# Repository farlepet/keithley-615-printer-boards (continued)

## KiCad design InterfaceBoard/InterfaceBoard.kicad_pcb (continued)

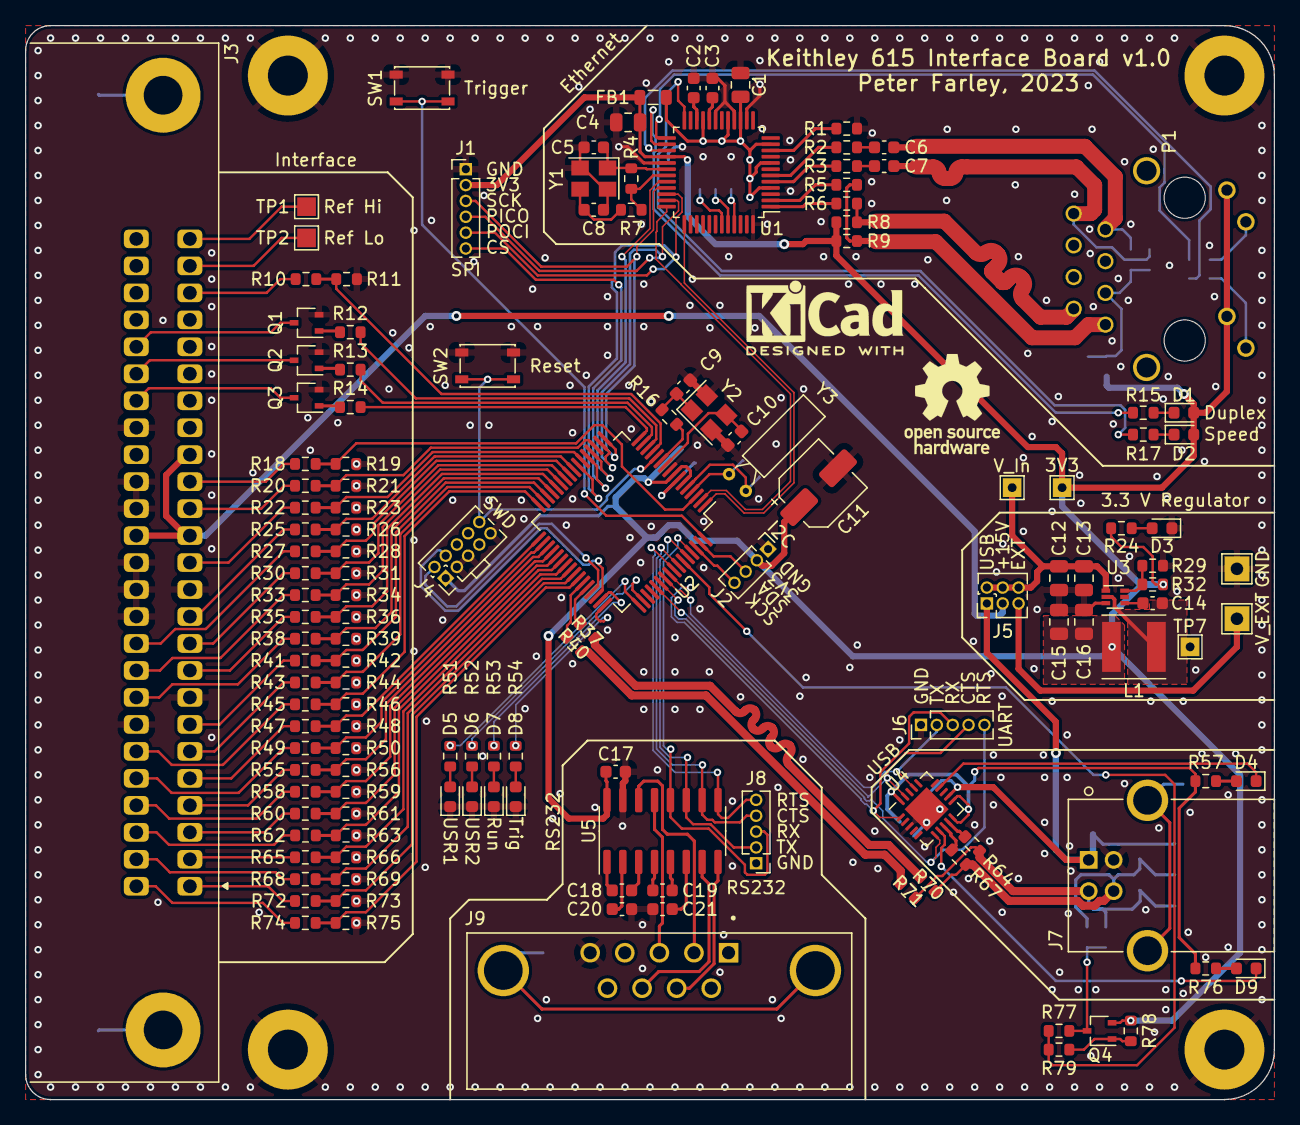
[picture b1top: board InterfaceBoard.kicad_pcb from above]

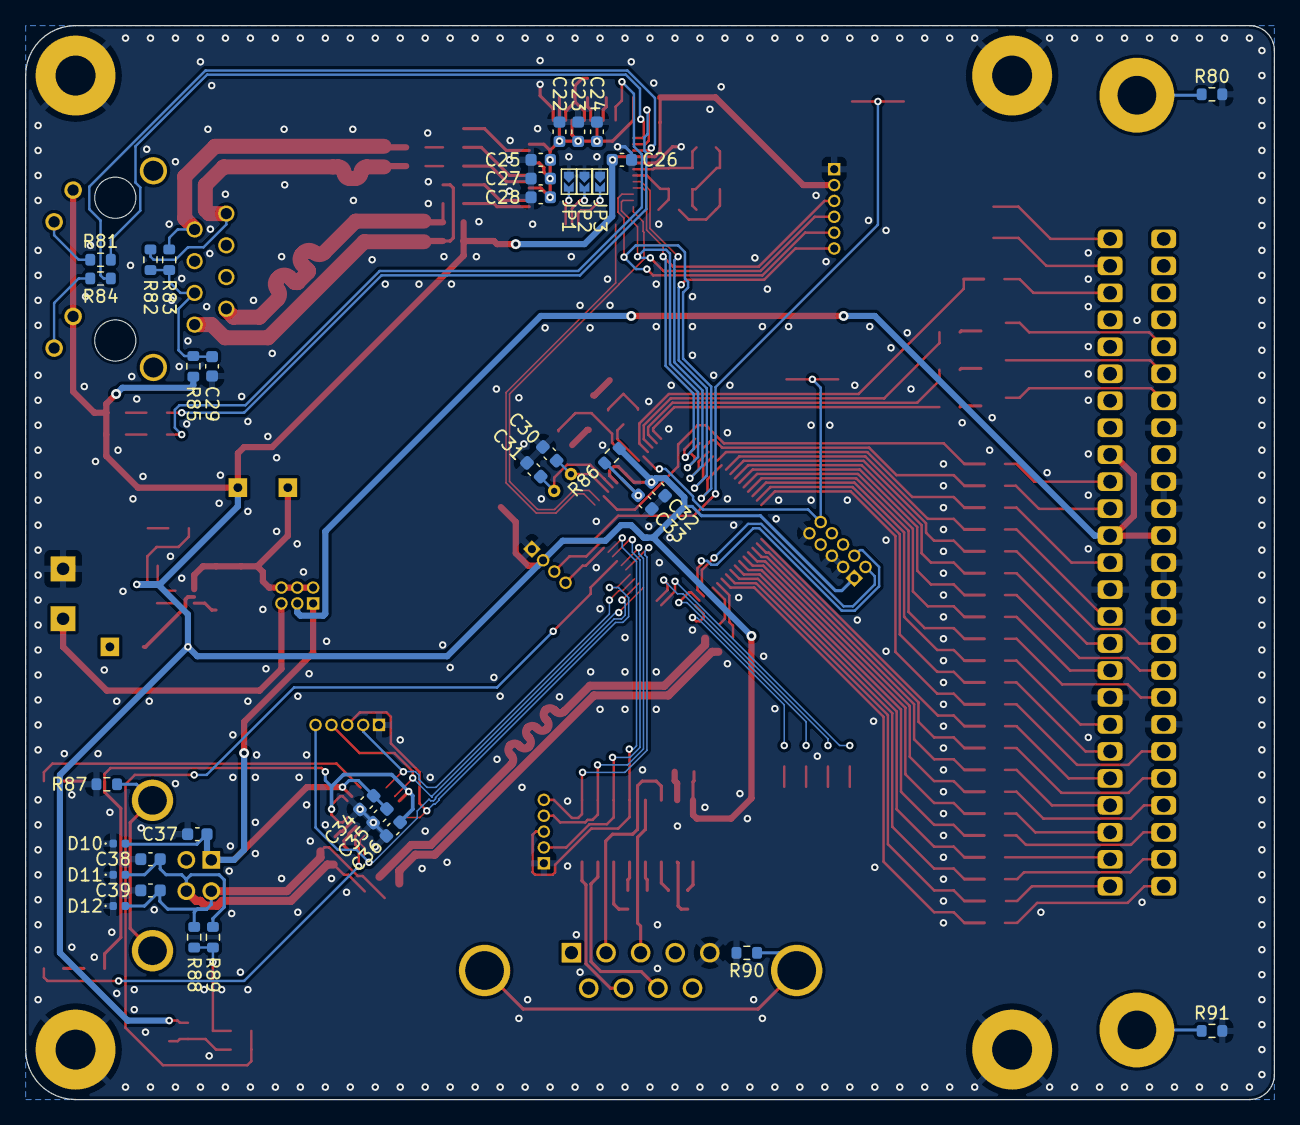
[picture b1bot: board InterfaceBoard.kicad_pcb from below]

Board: 2 copper layers, 100.0 x 86.0 mm, 182 parts (36 on the bottom side), 161 nets.

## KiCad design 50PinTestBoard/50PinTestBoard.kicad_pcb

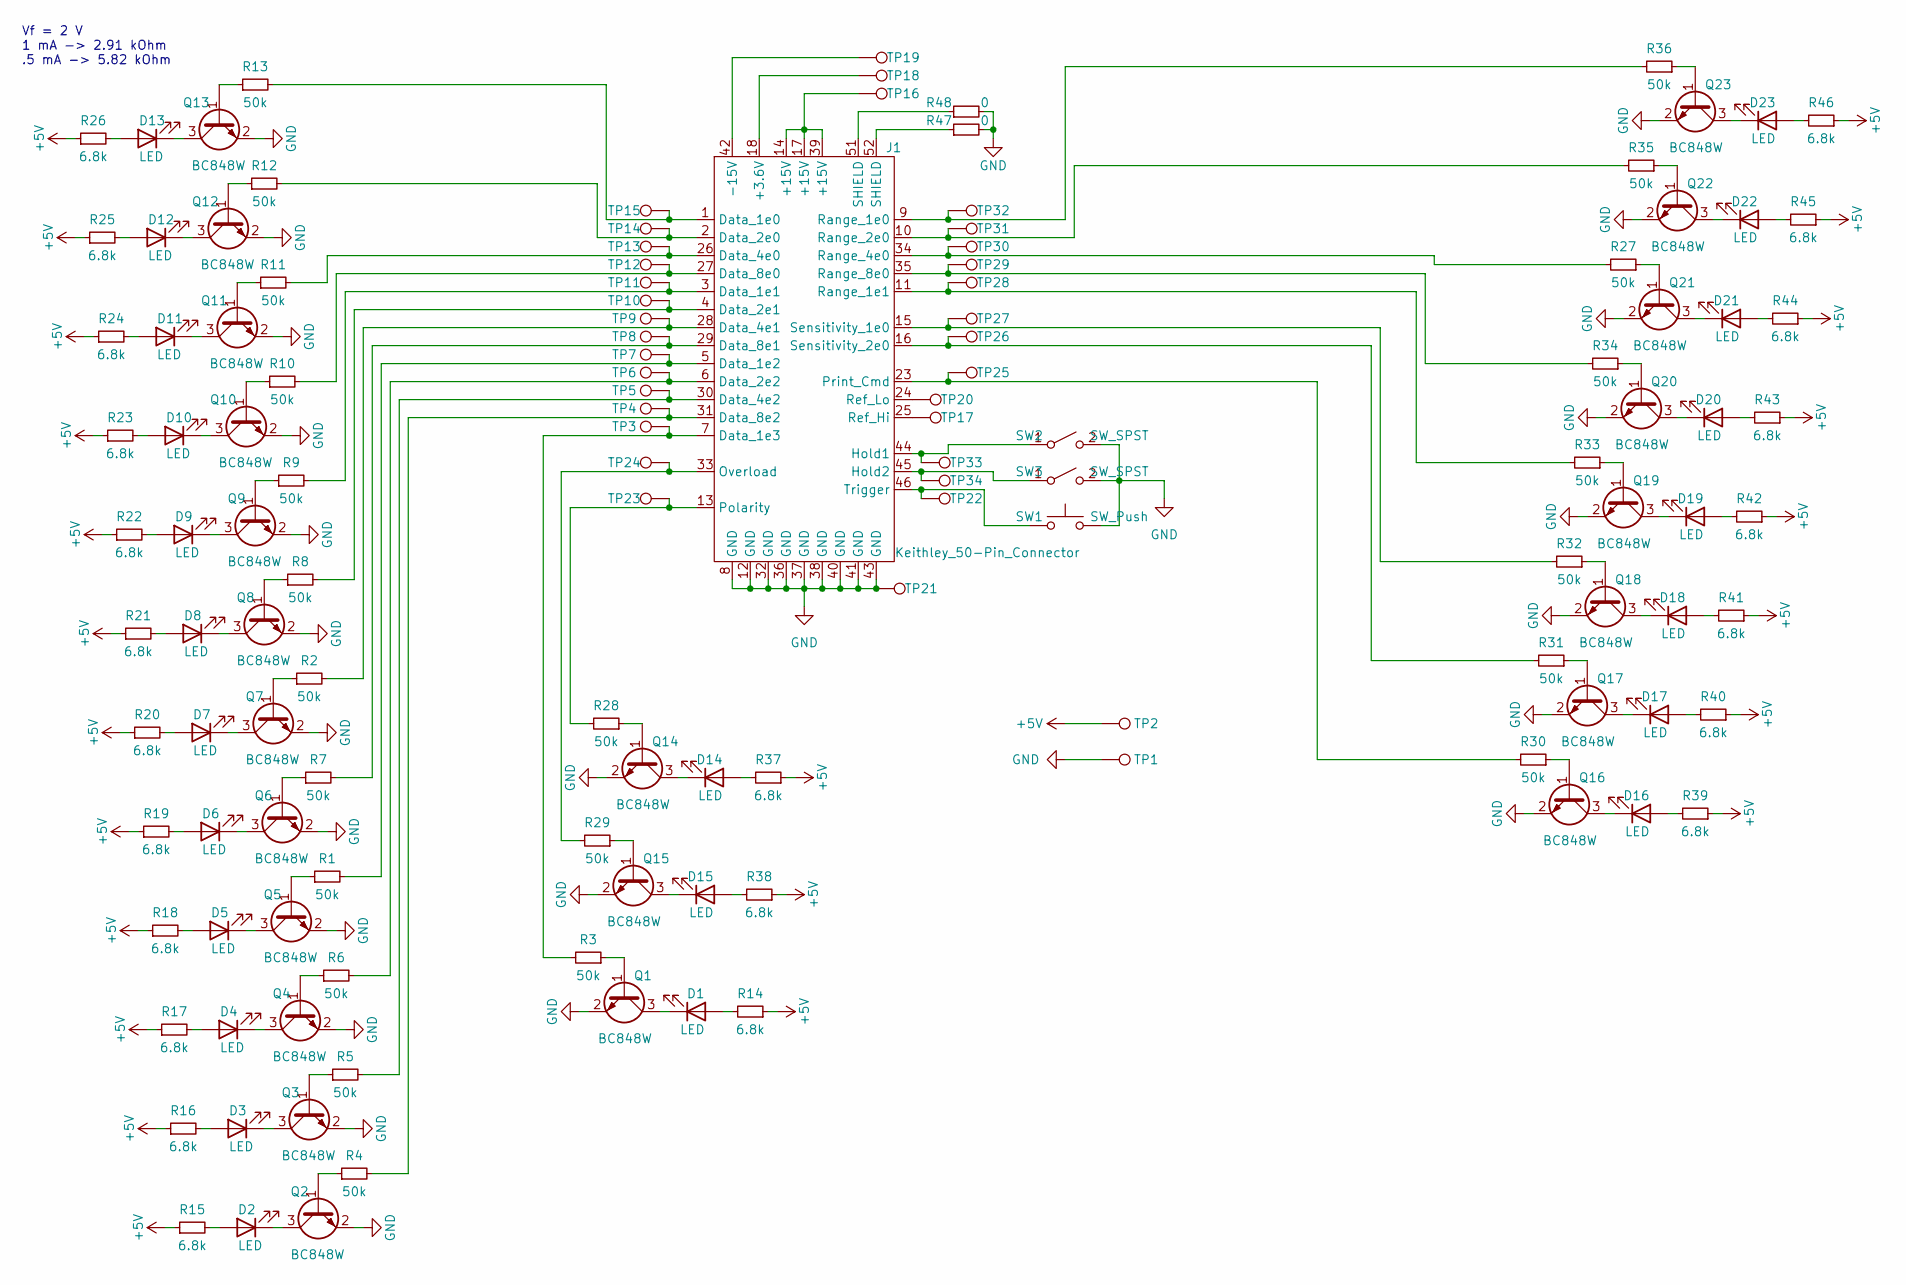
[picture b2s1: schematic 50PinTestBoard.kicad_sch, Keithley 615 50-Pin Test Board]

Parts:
D1, D2, D3, D4, D5, D6, D7, D8, D9, D10, D11, D12, D13, D14, D15, D16, D17, D18, D19, D20, D21, D22, D23: LED; LED_0603_1608Metric
J1: Keithley_50-Pin_Connector; NorComp_112-050-213R001
Q1, Q2, Q3, Q4, Q5, Q6, Q7, Q8, Q9, Q10, Q11, Q12, Q13, Q14, Q15, Q16, Q17, Q18, Q19, Q20, Q21, Q22, Q23: BC848W; SOT-323_SC-70
R1, R2, R3, R4, R5, R6, R7, R8, R9, R10, R11, R12, R13, R27, R28, R29, R30, R31, R32, R33, R34, R35, R36: 50k; R_0603_1608Metric
R14, R15, R16, R17, R18, R19, R20, R21, R22, R23, R24, R25, R26, R37, R38, R39, R40, R41, R42, R43, R44, R45, R46: 6.8k; R_0603_1608Metric
R47, R48: 0; R_0603_1608Metric
SW1: SW_Push; SW_SPST_PTS810
SW2, SW3: SW_SPST; SW_SPDT_CK-JS102011SAQN
TP1, TP2, TP3, TP4, TP5, TP6, TP7, TP8, TP9, TP10, TP11, TP12, TP13, TP14, TP15, TP16, TP17, TP18, TP19, TP20, TP21, TP22, TP23, TP24, TP25, TP26, TP27, TP28, TP29, TP30, TP31, TP32, TP33, TP34: TestPoint; TestPoint_THTPad_2.0x2.0mm_Drill1.0mm

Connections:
+5V: R14.1, R15.1, R16.1, R17.1, R18.1, R19.1, R20.1, R21.1, R22.1, R23.1, R24.1, R25.1, R26.1, R37.1, R38.1, R39.1, R40.1, R41.1, R42.1, R43.1, R44.1, R45.1, R46.1, TP2.1
GND: J1.8 (GND), J1.12 (GND), J1.32 (GND), J1.36 (GND), J1.37 (GND), J1.38 (GND), J1.40 (GND), J1.41 (GND), J1.43 (GND), Q1.2 (E), Q2.2 (E), Q3.2 (E), Q4.2 (E), Q5.2 (E), Q6.2 (E), Q7.2 (E), Q8.2 (E), Q9.2 (E), Q10.2 (E), Q11.2 (E), Q12.2 (E), Q13.2 (E), Q14.2 (E), Q15.2 (E), Q16.2 (E), Q17.2 (E), Q18.2 (E), Q19.2 (E), Q20.2 (E), Q21.2 (E), Q22.2 (E), Q23.2 (E), R47.2, R48.2, SW1.2, SW2.2 (B), SW3.2 (B), TP1.1, TP21.1
unnamed: D1.1 (K), Q1.3 (C)
unnamed: D1.2 (A), R14.2
unnamed: D2.1 (K), Q2.3 (C)
unnamed: D2.2 (A), R15.2
unnamed: D3.1 (K), Q3.3 (C)
unnamed: D3.2 (A), R16.2
unnamed: D4.1 (K), Q4.3 (C)
unnamed: D4.2 (A), R17.2
unnamed: D5.1 (K), Q5.3 (C)
unnamed: D5.2 (A), R18.2
unnamed: D6.1 (K), Q6.3 (C)
unnamed: D6.2 (A), R19.2
unnamed: D7.1 (K), Q7.3 (C)
unnamed: D7.2 (A), R20.2
unnamed: D8.1 (K), Q8.3 (C)
unnamed: D8.2 (A), R21.2
unnamed: D9.1 (K), Q9.3 (C)
unnamed: D9.2 (A), R22.2
unnamed: D10.1 (K), Q10.3 (C)
unnamed: D10.2 (A), R23.2
unnamed: D11.1 (K), Q11.3 (C)
unnamed: D11.2 (A), R24.2
unnamed: D12.1 (K), Q12.3 (C)
unnamed: D12.2 (A), R25.2
unnamed: D13.1 (K), Q13.3 (C)
unnamed: D13.2 (A), R26.2
unnamed: D14.1 (K), Q14.3 (C)
unnamed: D14.2 (A), R37.2
unnamed: D15.1 (K), Q15.3 (C)
unnamed: D15.2 (A), R38.2
unnamed: D16.1 (K), Q16.3 (C)
unnamed: D16.2 (A), R39.2
unnamed: D17.1 (K), Q17.3 (C)
unnamed: D17.2 (A), R40.2
unnamed: D18.1 (K), Q18.3 (C)
unnamed: D18.2 (A), R41.2
unnamed: D19.1 (K), Q19.3 (C)
unnamed: D19.2 (A), R42.2
unnamed: D20.1 (K), Q20.3 (C)
unnamed: D20.2 (A), R43.2
unnamed: D21.1 (K), Q21.3 (C)
unnamed: D21.2 (A), R44.2
unnamed: D22.1 (K), Q22.3 (C)
unnamed: D22.2 (A), R45.2
unnamed: D23.1 (K), Q23.3 (C)
unnamed: D23.2 (A), R46.2
unnamed: J1.1 (Data_1e0), R13.2, TP15.1
unnamed: J1.2 (Data_2e0), R12.2, TP14.1
unnamed: J1.3 (Data_1e1), R9.2, TP11.1
unnamed: J1.4 (Data_2e1), R8.2, TP10.1
unnamed: J1.5 (Data_1e2), R1.2, TP7.1
unnamed: J1.6 (Data_2e2), R6.2, TP6.1
unnamed: J1.7 (Data_1e3), R3.2, TP3.1
unnamed: J1.9 (Range_1e0), R36.2, TP32.1
unnamed: J1.10 (Range_2e0), R35.2, TP31.1
unnamed: J1.11 (Range_1e1), R33.2, TP28.1
unnamed: J1.13 (Polarity), R28.2, TP23.1
unnamed: J1.14 (+15V), J1.17 (+15V), J1.39 (+15V), TP16.1
unnamed: J1.15 (Sensitivity_1e0), R32.2, TP27.1
unnamed: J1.16 (Sensitivity_2e0), R31.2, TP26.1
unnamed: J1.18 (+3.6V), TP18.1
unnamed: J1.23 (Print_Cmd), R30.2, TP25.1
unnamed: J1.24 (Ref_Lo), TP20.1
unnamed: J1.25 (Ref_Hi), TP17.1
unnamed: J1.26 (Data_4e0), R11.2, TP13.1
unnamed: J1.27 (Data_8e0), R10.2, TP12.1
unnamed: J1.28 (Data_4e1), R2.2, TP9.1
unnamed: J1.29 (Data_8e1), R7.2, TP8.1
unnamed: J1.30 (Data_4e2), R5.2, TP5.1
unnamed: J1.31 (Data_8e2), R4.2, TP4.1
unnamed: J1.33 (Overload), R29.2, TP24.1
unnamed: J1.34 (Range_4e0), R27.2, TP30.1
unnamed: J1.35 (Range_8e0), R34.2, TP29.1
unnamed: J1.42 (-15V), TP19.1
unnamed: J1.44 (Hold1), SW2.1 (A), TP33.1
unnamed: J1.45 (Hold2), SW3.1 (A), TP34.1
unnamed: J1.46 (Trigger), SW1.1, TP22.1
unnamed: J1.51 (SHIELD), R48.1
unnamed: J1.52 (SHIELD), R47.1
unnamed: Q1.1 (B), R3.1
unnamed: Q2.1 (B), R4.1
unnamed: Q3.1 (B), R5.1
unnamed: Q4.1 (B), R6.1
unnamed: Q5.1 (B), R1.1
unnamed: Q6.1 (B), R7.1
unnamed: Q7.1 (B), R2.1
unnamed: Q8.1 (B), R8.1
unnamed: Q9.1 (B), R9.1
unnamed: Q10.1 (B), R10.1
unnamed: Q11.1 (B), R11.1
unnamed: Q12.1 (B), R12.1
unnamed: Q13.1 (B), R13.1
unnamed: Q14.1 (B), R28.1
unnamed: Q15.1 (B), R29.1
unnamed: Q16.1 (B), R30.1
unnamed: Q17.1 (B), R31.1
unnamed: Q18.1 (B), R32.1
unnamed: Q19.1 (B), R33.1
unnamed: Q20.1 (B), R34.1
unnamed: Q21.1 (B), R27.1
unnamed: Q22.1 (B), R35.1
unnamed: Q23.1 (B), R36.1

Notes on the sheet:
Vf = 2 V 1 mA -> 2.91 kOhm .5 mA -> 5.82 kOhm

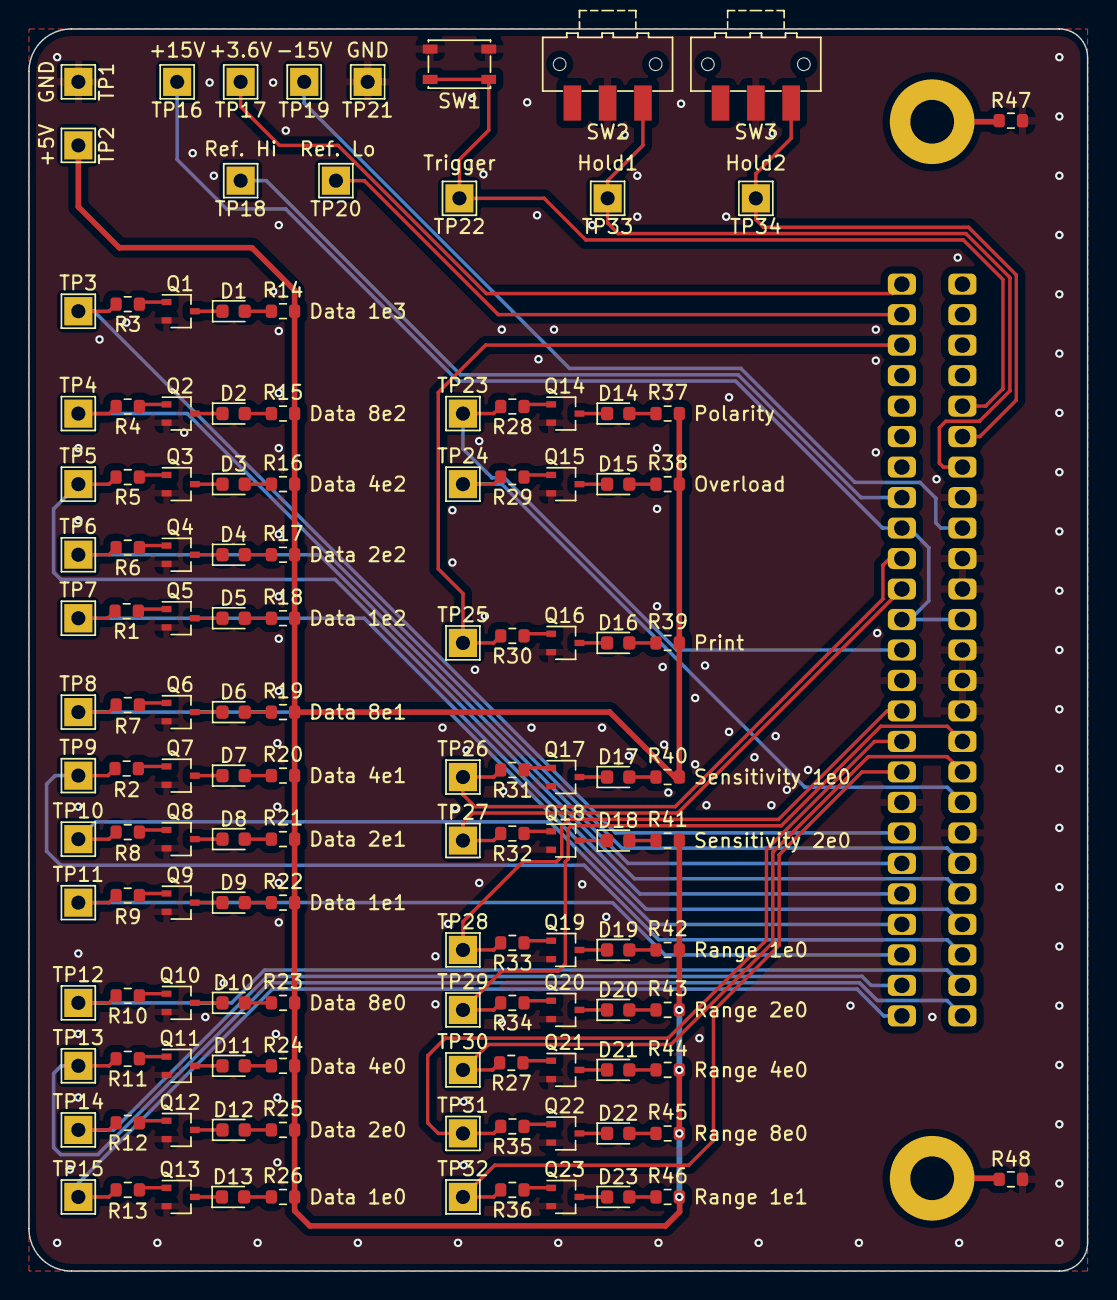
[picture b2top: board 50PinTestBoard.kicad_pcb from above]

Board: 2 copper layers, 75.0 x 88.0 mm, 132 parts (1 on the bottom side), 104 nets.

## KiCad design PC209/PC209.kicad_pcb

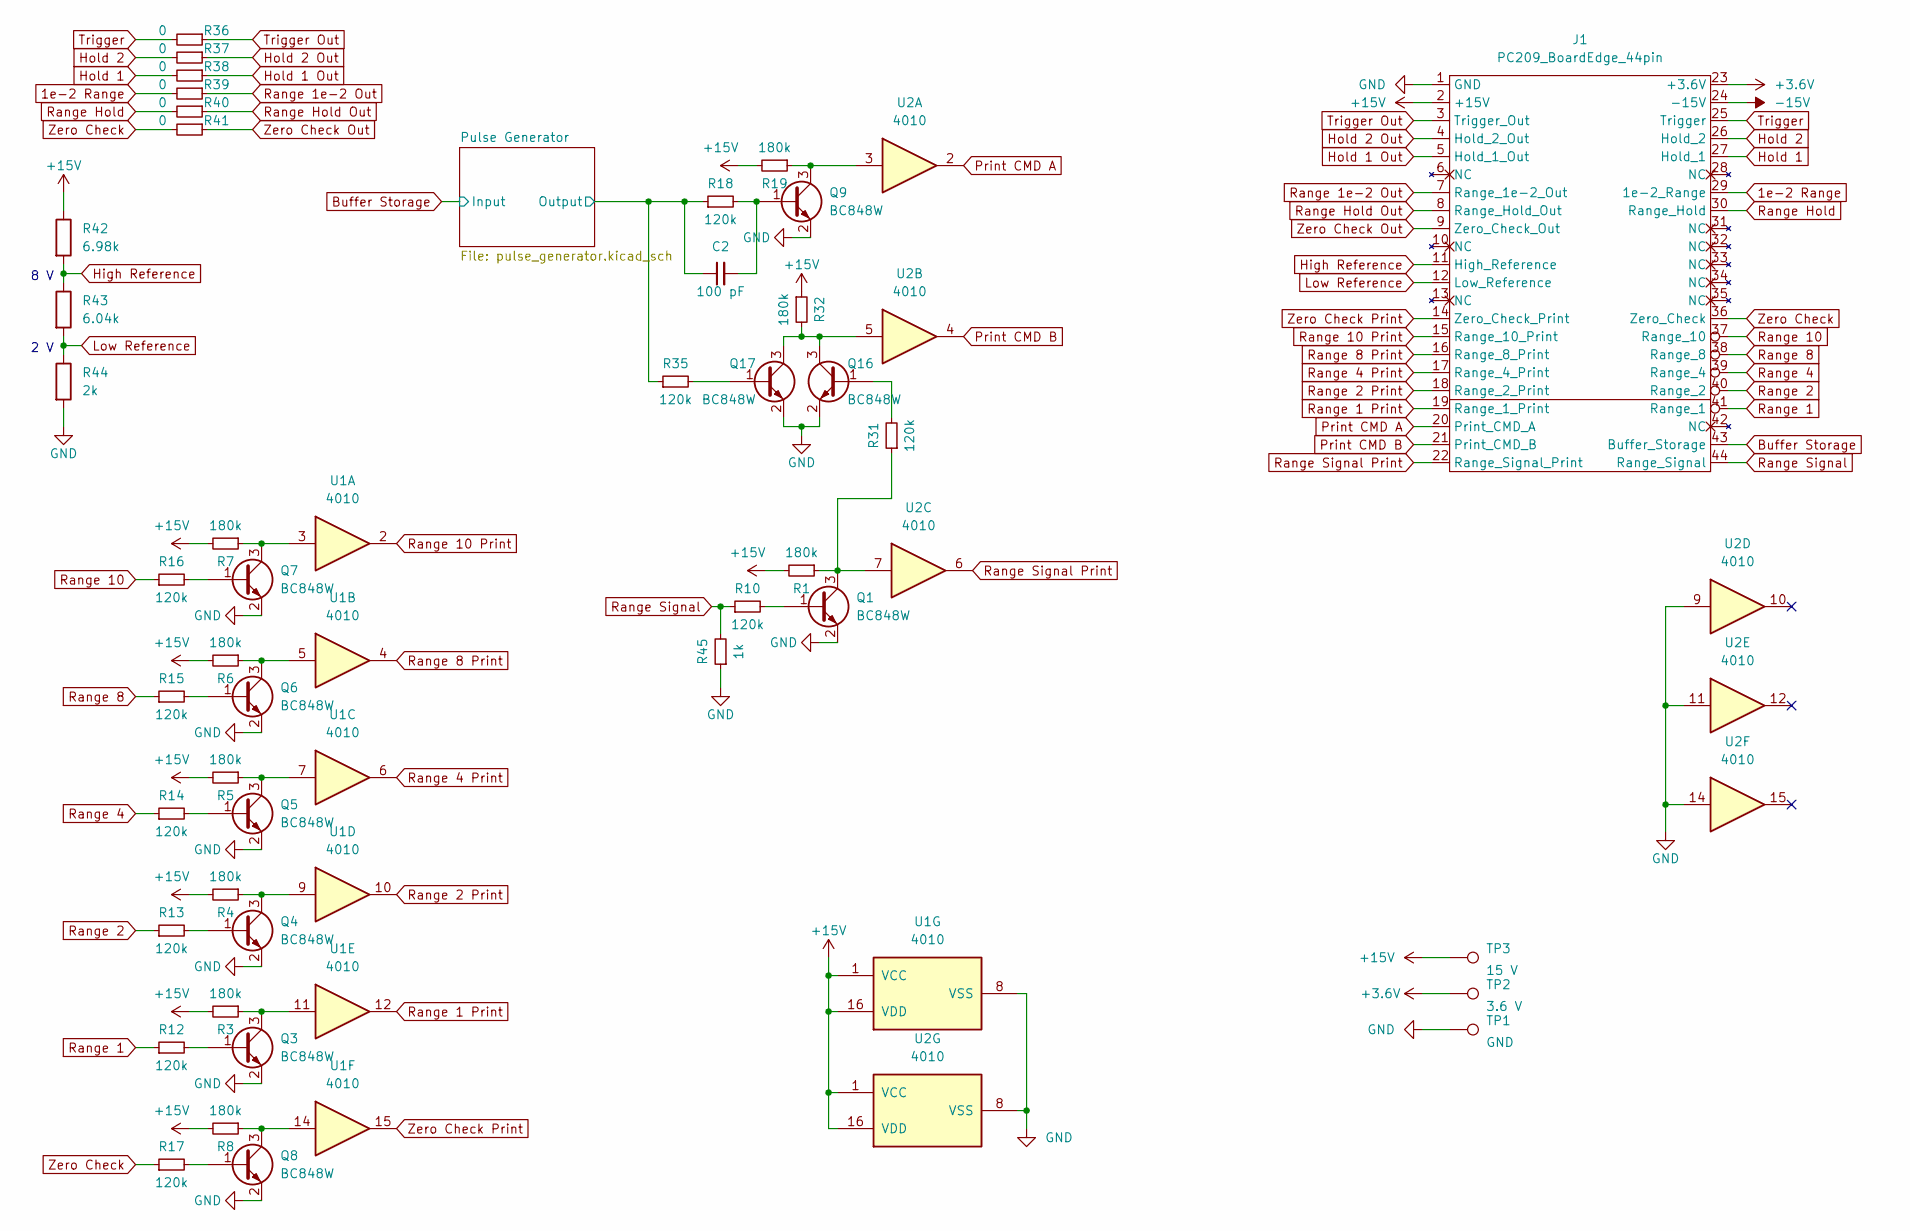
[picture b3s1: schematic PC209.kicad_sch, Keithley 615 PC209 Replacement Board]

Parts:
C2: 100 pF; C_0603_1608Metric
J1: PC209_BoardEdge_44pin; PC209_Edge_Connector
Q1, Q3, Q4, Q5, Q6, Q7, Q8, Q9, Q16, Q17: BC848W; SOT-323_SC-70
R1, R3, R4, R5, R6, R7, R8, R19, R32: 180k; R_0603_1608Metric
R10, R12, R13, R14, R15, R16, R17, R18, R31, R35: 120k; R_0603_1608Metric
R36, R37, R38, R39, R40, R41: 0; R_0603_1608Metric
R42: 6.98k; R_0603_1608Metric
R43: 6.04k; R_0603_1608Metric
R44: 2k; R_0603_1608Metric
R45: 1k; R_0603_1608Metric
TP1: GND; TestPoint_THTPad_2.0x2.0mm_Drill1.0mm
TP2: 3.6 V; TestPoint_THTPad_2.0x2.0mm_Drill1.0mm
TP3: 15 V; TestPoint_THTPad_2.0x2.0mm_Drill1.0mm
U1, U2: 4010; SOIC-16_3.9x9.9mm_P1.27mm

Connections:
1e-2 Range: J1.29 (1e-2_Range), R39.2
+3.6V: J1.23 (+3.6V), TP2.1; also elsewhere on the board
+15V: J1.2 (+15V), R1.2, R3.2, R4.2, R5.2, R6.2, R7.2, R8.2, R19.2, R32.1, R42.1, TP3.1, U1.1 (VCC), U1.16 (VDD), U2.1 (VCC), U2.16 (VDD)
-15V: J1.24 (-15V)
/Pulse Generator/Output: C2.1, R18.1, R35.1; also elsewhere on the board
Buffer Storage: J1.43 (Buffer_Storage); also elsewhere on the board
GND: J1.1 (GND), Q1.2 (E), Q3.2 (E), Q4.2 (E), Q5.2 (E), Q6.2 (E), Q7.2 (E), Q8.2 (E), Q9.2 (E), Q16.2 (E), Q17.2 (E), R44.2, R45.1, TP1.1, U1.8 (VSS), U2.8 (VSS), U2.9, U2.11, U2.14; also elsewhere on the board
High Reference: J1.11 (High_Reference), R42.2, R43.1
Hold 1: J1.27 (Hold_1), R38.2
Hold 1 Out: J1.5 (Hold_1_Out), R38.1
Hold 2: J1.26 (Hold_2), R37.2
Hold 2 Out: J1.4 (Hold_2_Out), R37.1
Low Reference: J1.12 (Low_Reference), R43.2, R44.1
unnamed: C2.2, Q9.1 (B), R18.2
unnamed: Q1.1 (B), R10.2
unnamed: Q1.3 (C), R1.1, R31.1, U2.7
unnamed: Q3.1 (B), R12.2
unnamed: Q3.3 (C), R3.1, U1.11
unnamed: Q4.1 (B), R13.2
unnamed: Q4.3 (C), R4.1, U1.9
unnamed: Q5.1 (B), R14.2
unnamed: Q5.3 (C), R5.1, U1.7
unnamed: Q6.1 (B), R15.2
unnamed: Q6.3 (C), R6.1, U1.5
unnamed: Q7.1 (B), R16.2
unnamed: Q7.3 (C), R7.1, U1.3
unnamed: Q8.1 (B), R17.2
unnamed: Q8.3 (C), R8.1, U1.14
unnamed: Q9.3 (C), R19.1, U2.3
unnamed: Q16.1 (B), R31.2
unnamed: Q16.3 (C), Q17.3 (C), R32.2, U2.5
unnamed: Q17.1 (B), R35.2
Print CMD A: J1.20 (Print_CMD_A), U2.2
Print CMD B: J1.21 (Print_CMD_B), U2.4
Range 1: J1.41 (Range_1), R12.1
Range 1 Print: J1.19 (Range_1_Print), U1.12
Range 1e-2 Out: J1.7 (Range_1e-2_Out), R39.1
Range 2: J1.40 (Range_2), R13.1
Range 2 Print: J1.18 (Range_2_Print), U1.10
Range 4: J1.39 (Range_4), R14.1
Range 4 Print: J1.17 (Range_4_Print), U1.6
Range 8: J1.38 (Range_8), R15.1
Range 8 Print: J1.16 (Range_8_Print), U1.4
Range 10: J1.37 (Range_10), R16.1
Range 10 Print: J1.15 (Range_10_Print), U1.2
Range Hold: J1.30 (Range_Hold), R40.2
Range Hold Out: J1.8 (Range_Hold_Out), R40.1
Range Signal: J1.44 (Range_Signal), R10.1, R45.2
Range Signal Print: J1.22 (Range_Signal_Print), U2.6
Trigger: J1.25 (Trigger), R36.2
Trigger Out: J1.3 (Trigger_Out), R36.1
Zero Check: J1.36 (Zero_Check), R17.1, R41.2
Zero Check Out: J1.9 (Zero_Check_Out), R41.1
Zero Check Print: J1.14 (Zero_Check_Print), U1.15

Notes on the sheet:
2 V
8 V

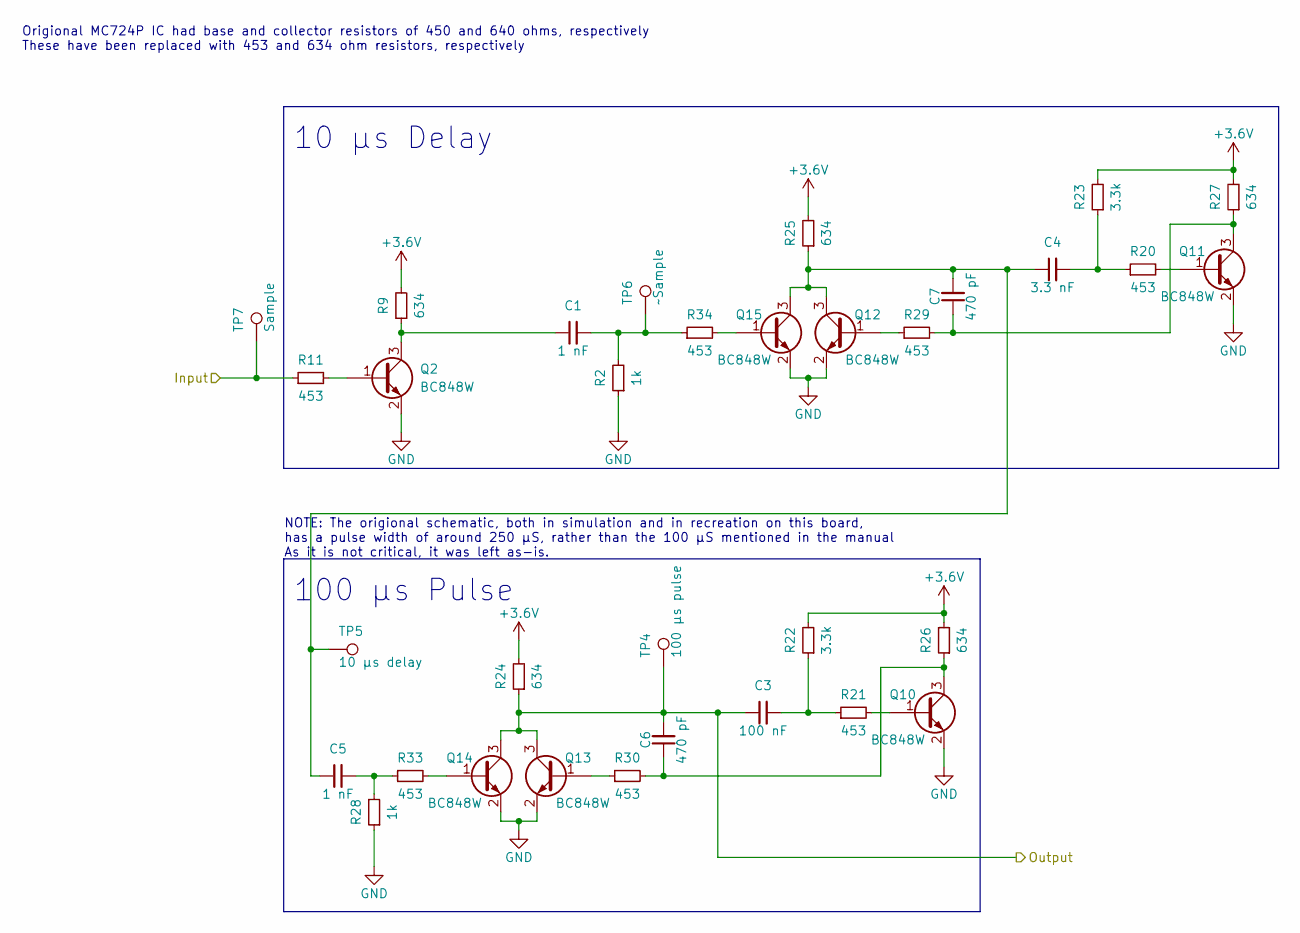
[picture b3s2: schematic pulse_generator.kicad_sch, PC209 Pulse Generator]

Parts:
C1, C5: 1 nF; C_0603_1608Metric
C3: 100 nF; C_0603_1608Metric
C4: 3.3 nF; C_0603_1608Metric
C6, C7: 470 pF; C_0603_1608Metric
Q2, Q10, Q11, Q12, Q13, Q14, Q15: BC848W; SOT-323_SC-70
R2, R28: 1k; R_0603_1608Metric
R9, R24, R25, R26, R27: 634; R_0603_1608Metric
R11, R20, R21, R29, R30, R33, R34: 453; R_0603_1608Metric
R22, R23: 3.3k; R_0603_1608Metric
TP4: 100 μs pulse; TestPoint_THTPad_2.0x2.0mm_Drill1.0mm
TP5: 10 μs delay; TestPoint_THTPad_2.0x2.0mm_Drill1.0mm
TP6: ~Sample; TestPoint_THTPad_2.0x2.0mm_Drill1.0mm
TP7: Sample; TestPoint_THTPad_2.0x2.0mm_Drill1.0mm

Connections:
+3.6V: R9.2, R22.2, R23.2, R24.2, R25.2, R26.2, R27.2; also elsewhere on the board
/Pulse Generator/Output: C3.1, C6.2, Q13.3 (C), Q14.3 (C), R24.1, TP4.1; also elsewhere on the board
Buffer Storage: R11.1, TP7.1; also elsewhere on the board
GND: Q2.2 (E), Q10.2 (E), Q11.2 (E), Q12.2 (E), Q13.2 (E), Q14.2 (E), Q15.2 (E), R2.1, R28.1; also elsewhere on the board
unnamed: C1.1, Q2.3 (C), R9.1
unnamed: C1.2, R2.2, R34.1, TP6.1
unnamed: C3.2, R21.1, R22.1
unnamed: C4.1, C5.1, C7.2, Q12.3 (C), Q15.3 (C), R25.1, TP5.1
unnamed: C4.2, R20.1, R23.1
unnamed: C5.2, R28.2, R33.1
unnamed: C6.1, Q10.3 (C), R26.1, R30.2
unnamed: C7.1, Q11.3 (C), R27.1, R29.2
unnamed: Q2.1 (B), R11.2
unnamed: Q10.1 (B), R21.2
unnamed: Q11.1 (B), R20.2
unnamed: Q12.1 (B), R29.1
unnamed: Q13.1 (B), R30.1
unnamed: Q14.1 (B), R33.2
unnamed: Q15.1 (B), R34.2

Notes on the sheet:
NOTE: The origional schematic, both in simulation and in recreation on this board, has a pulse width of around 250 μS, rather than the 100 μS mentioned in the manual As it is not critical, it was left as-is.
10 μs Delay
100 μs Pulse
Origional MC724P IC had base and collector resistors of 450 and 640 ohms, respectively These have been replaced with 453 and 634 ohm resistors, respectively

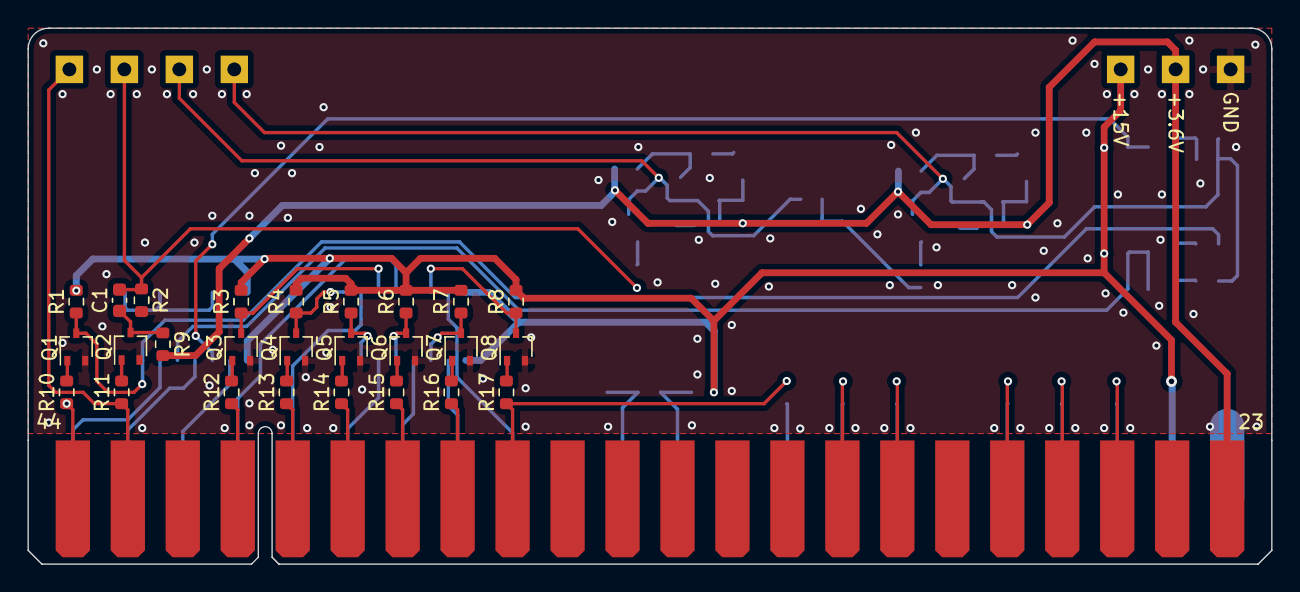
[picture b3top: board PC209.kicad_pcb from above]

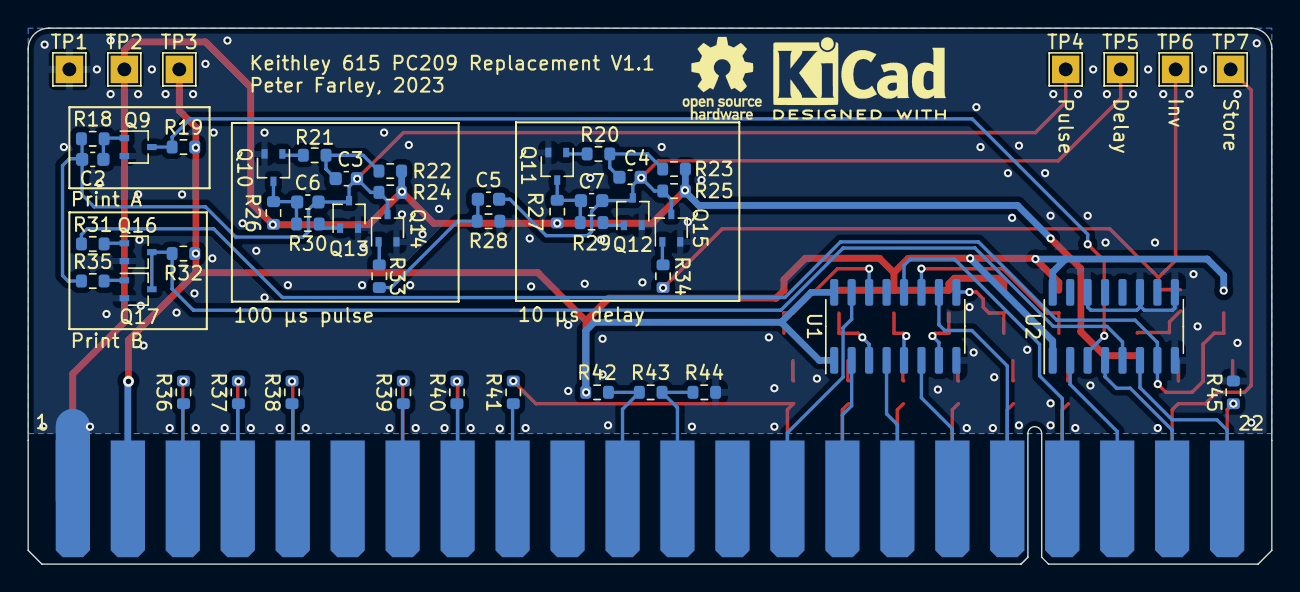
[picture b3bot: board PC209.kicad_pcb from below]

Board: 2 copper layers, 90.5 x 39.0 mm, 79 parts (52 on the bottom side), 68 nets.

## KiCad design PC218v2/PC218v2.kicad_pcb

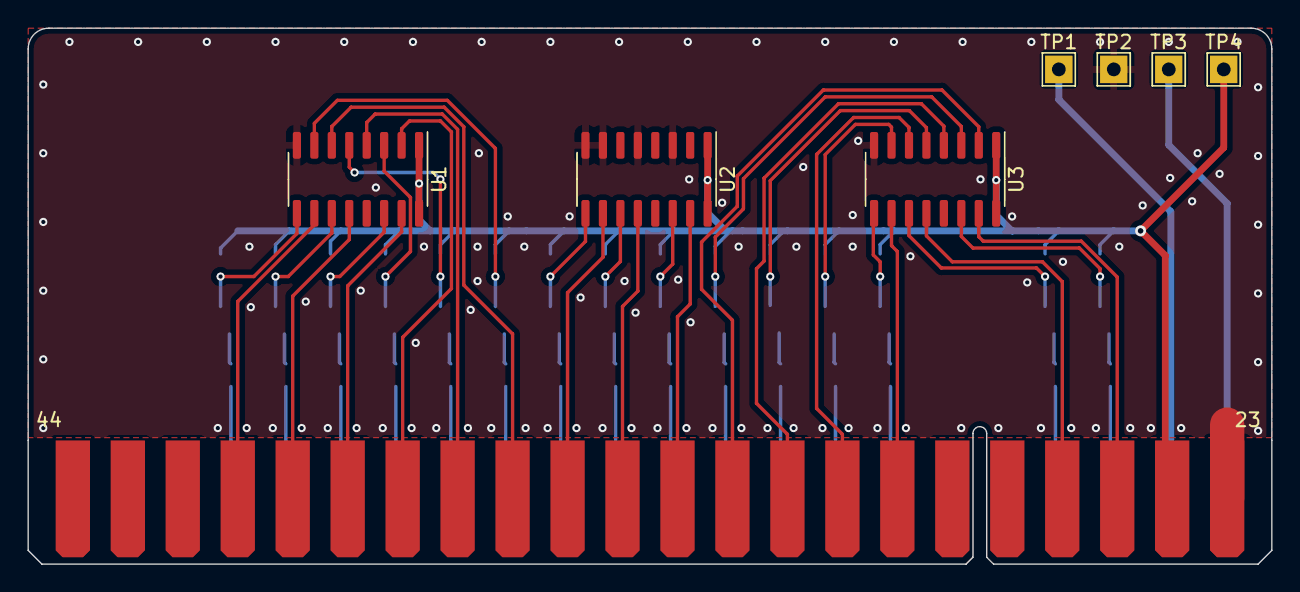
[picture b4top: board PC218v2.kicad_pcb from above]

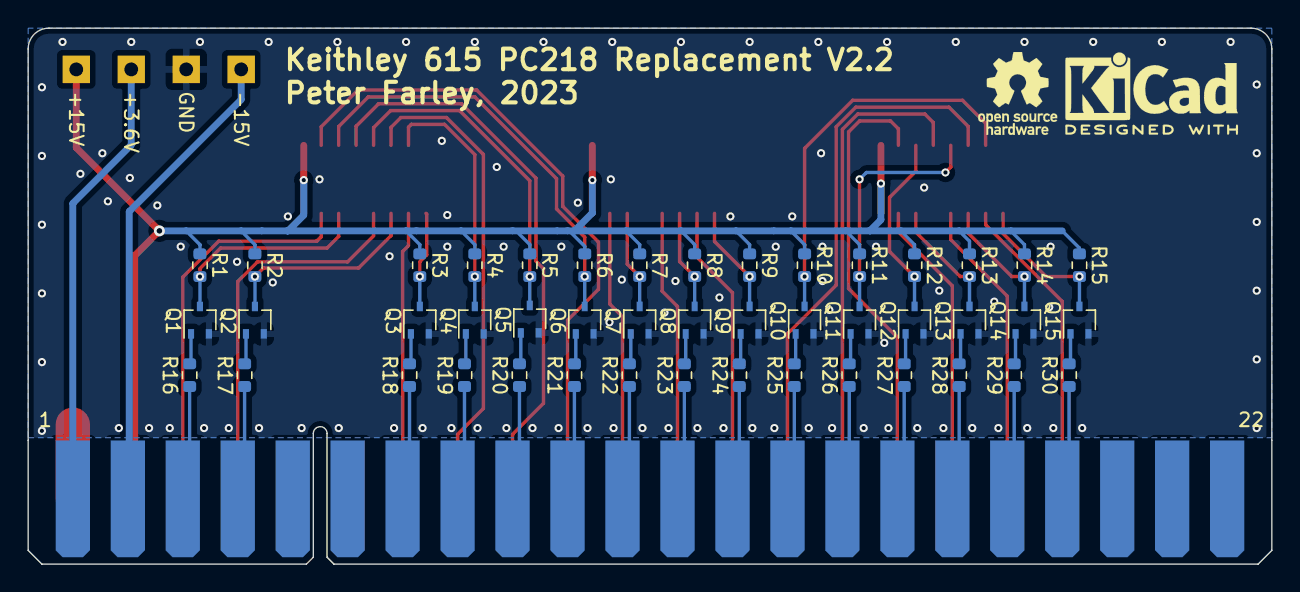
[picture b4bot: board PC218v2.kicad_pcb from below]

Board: 2 copper layers, 90.5 x 39.0 mm, 53 parts (45 on the bottom side), 64 nets.

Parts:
J1: PC218_BoardEdge_44pin; PC218_Edge_Connector
Q1, Q2, Q3, Q4, Q5, Q6, Q7, Q8, Q9, Q10, Q11, Q12, Q13, Q14, Q15: BC848W; SOT-323_SC-70
R1, R2, R3, R4, R5, R6, R7, R8, R9, R10, R11, R12, R13, R14, R15: 180K; R_0603_1608Metric
R16, R17, R18, R19, R20, R21, R22, R23, R24, R25, R26, R27, R28, R29, R30: 120K; R_0603_1608Metric
TP1: -15V; TestPoint_THTPad_2.0x2.0mm_Drill1.0mm
TP2: GND; TestPoint_THTPad_2.0x2.0mm_Drill1.0mm
TP3: 3.6V; TestPoint_THTPad_2.0x2.0mm_Drill1.0mm
TP4: 15V; TestPoint_THTPad_2.0x2.0mm_Drill1.0mm
U1, U2, U3: 4010; SOIC-16_3.9x9.9mm_P1.27mm

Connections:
1x10^0: J1.13 (1x10^0), R24.1
1x10^0 Print: J1.35 (1x10^0_Print), U2.10
1x10^1: J1.18 (1x10^1), R29.1
1x10^1 Print: J1.40 (1x10^1_Print), U1.12
1x10^2: J1.9 (1x10^2), R20.1
1x10^2 Print: J1.31 (1x10^2_Print), U3.4
1x10^3: J1.7 (1x10^3), R18.1
1x10^3 Print: J1.29 (1x10^3_Print), U3.10
2x10^0: J1.12 (2x10^0), R23.1
2x10^0 Print: J1.34 (2x10^0_Print), U2.12
2x10^1: J1.19 (2x10^1), R30.1
2x10^1 Print: J1.41 (2x10^1_Print), U1.10
2x10^2: J1.8 (2x10^2), R19.1
2x10^2 Print: J1.30 (2x10^2_Print), U3.6
4x10^0: J1.14 (4x10^0), R25.1
4x10^0 Print: J1.36 (4x10^0_Print), U1.6
4x10^1: J1.17 (4x10^1), R28.1
4x10^1 Print: J1.39 (4x10^1_Print), U1.15
4x10^2: J1.10 (4x10^2), R21.1
4x10^2 Print: J1.32 (4x10^2_Print), U3.2
8x10^0: J1.15 (8x10^0), R26.1
8x10^0 Print: J1.37 (8x10^0_Print), U1.4
8x10^1: J1.16 (8x10^1), R27.1
8x10^1 Print: J1.38 (8x10^1_Print), U1.2
8x10^2: J1.11 (8x10^2), R22.1
8x10^2 Print: J1.33 (8x10^2_Print), U2.15
+3.6V: J1.1 (3.6V), TP3.1
+15V: J1.24 (+15V), R1.1, R2.1, R3.1, R4.1, R5.1, R6.1, R7.1, R8.1, R9.1, R10.1, R11.1, R12.1, R13.1, R14.1, R15.1, TP4.1, U1.1 (VCC), U1.16 (VDD), U2.1 (VCC), U2.16 (VDD), U3.1 (VCC), U3.16 (VDD)
-15V: J1.2 (-15V), TP1.1
GND: J1.23 (GND), Q1.2 (E), Q2.2 (E), Q3.2 (E), Q4.2 (E), Q5.2 (E), Q6.2 (E), Q7.2 (E), Q8.2 (E), Q9.2 (E), Q10.2 (E), Q11.2 (E), Q12.2 (E), Q13.2 (E), Q14.2 (E), Q15.2 (E), TP2.1, U1.8 (VSS), U2.3, U2.5, U2.7, U2.8 (VSS), U3.8 (VSS)
unnamed: Q1.1 (B), R16.2
unnamed: Q1.3 (C), R1.2, U3.14
unnamed: Q2.1 (B), R17.2
unnamed: Q2.3 (C), R2.2, U3.11
unnamed: Q3.1 (B), R18.2
unnamed: Q3.3 (C), R3.2, U3.9
unnamed: Q4.1 (B), R19.2
unnamed: Q4.3 (C), R4.2, U3.7
unnamed: Q5.1 (B), R20.2
unnamed: Q5.3 (C), R5.2, U3.5
unnamed: Q6.1 (B), R21.2
unnamed: Q6.3 (C), R6.2, U3.3
unnamed: Q7.1 (B), R22.2
unnamed: Q7.3 (C), R7.2, U2.14
unnamed: Q8.1 (B), R23.2
unnamed: Q8.3 (C), R8.2, U2.11
unnamed: Q9.1 (B), R24.2
unnamed: Q9.3 (C), R9.2, U2.9
unnamed: Q10.1 (B), R25.2
unnamed: Q10.3 (C), R10.2, U1.7
unnamed: Q11.1 (B), R26.2
unnamed: Q11.3 (C), R11.2, U1.5
unnamed: Q12.1 (B), R27.2
unnamed: Q12.3 (C), R12.2, U1.3
unnamed: Q13.1 (B), R28.2
unnamed: Q13.3 (C), R13.2, U1.14
unnamed: Q14.1 (B), R29.2
unnamed: Q14.3 (C), R14.2, U1.11
unnamed: Q15.1 (B), R30.2
unnamed: Q15.3 (C), R15.2, U1.9
Overload: J1.4 (Overload), R17.1
Overload Print: J1.26 (Overload_Print), U3.12
Polarity: J1.3 (Polarity), R16.1
Polarity Print: J1.25 (Polarity_Print), U3.15
